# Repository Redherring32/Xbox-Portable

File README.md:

# Xbox-Portable
Fully portable original (2001) Xbox handheld using real hardware

## License:

Licensed under
the TAPR Open Hardware License (www.tapr.org/OHL)

©Redherring32 2023-2024

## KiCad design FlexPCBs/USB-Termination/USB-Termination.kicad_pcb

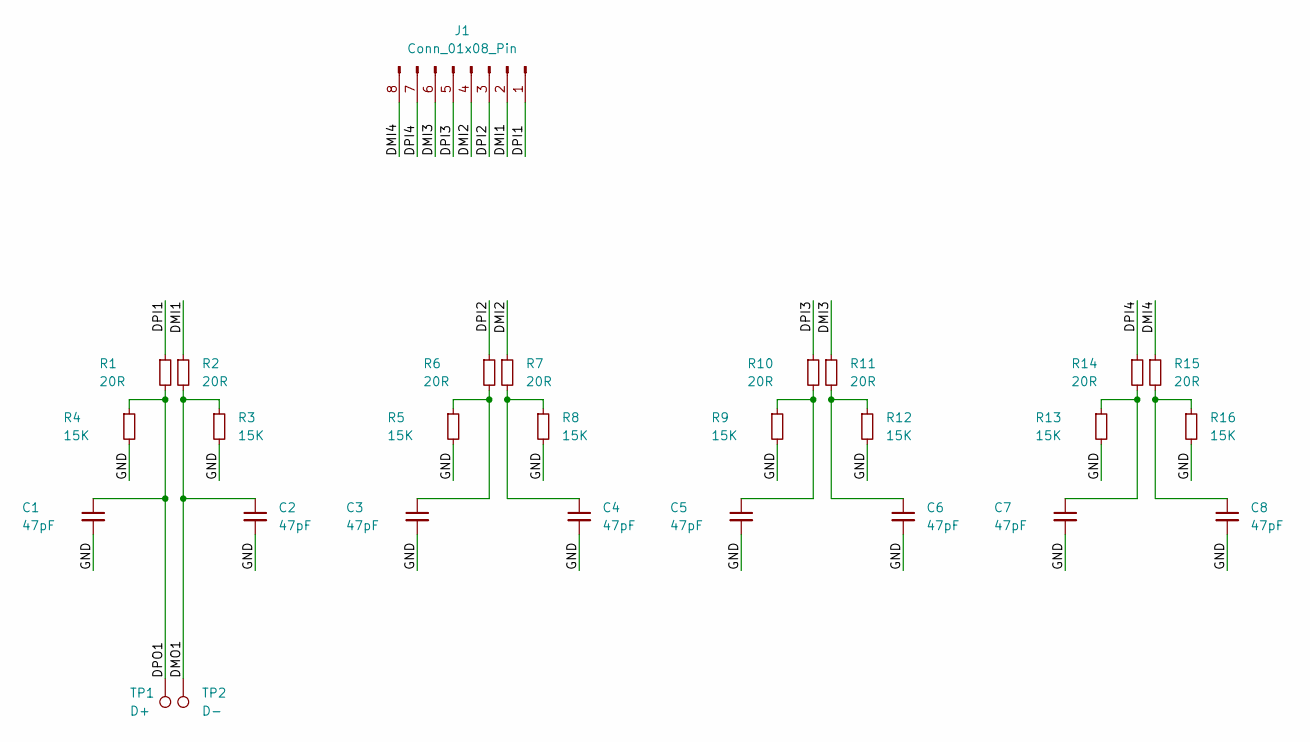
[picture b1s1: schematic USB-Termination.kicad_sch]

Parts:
C1, C2, C3, C4, C5, C6, C7, C8: 47pF; C_0201_0603Metric
J1: Conn_01x08_Pin; Vias
R1, R2, R6, R7, R10, R11, R14, R15: 20R; R_0201_0603Metric
R3, R4, R5, R8, R9, R12, R13, R16: 15K; R_0201_0603Metric
TP1: D+; TestPoint_Pad_D1.0mm
TP2: D-; TestPoint_Pad_D1.0mm

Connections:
/DMI1: J1.2, R2.1
/DMI2: J1.4, R7.1
/DMI3: J1.6, R11.1
/DMI4: J1.8, R15.1
/DMO1: C2.1, R2.2, R3.1, TP2.1
/DPI1: J1.1, R1.1
/DPI2: J1.3, R6.1
/DPI3: J1.5, R10.1
/DPI4: J1.7, R14.1
/DPO1: C1.1, R1.2, R4.1, TP1.1
/GND: C1.2, C2.2, C3.2, C4.2, C5.2, C6.2, C7.2, C8.2, R3.2, R4.2, R5.2, R8.2, R9.2, R12.2, R13.2, R16.2
unnamed: C3.1, R5.1, R6.2
unnamed: C4.1, R7.2, R8.1
unnamed: C5.1, R9.1, R10.2
unnamed: C6.1, R11.2, R12.1
unnamed: C7.1, R13.1, R14.2
unnamed: C8.1, R15.2, R16.1

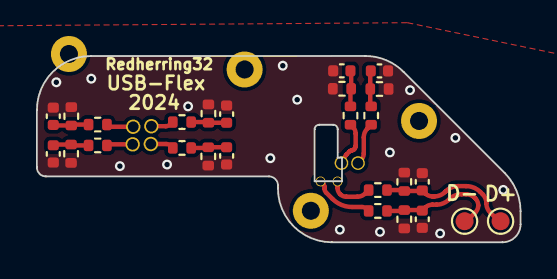
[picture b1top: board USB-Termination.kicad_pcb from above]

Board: 2 copper layers, 26.9 x 10.3 mm, 27 parts (1 on the bottom side), 17 nets.

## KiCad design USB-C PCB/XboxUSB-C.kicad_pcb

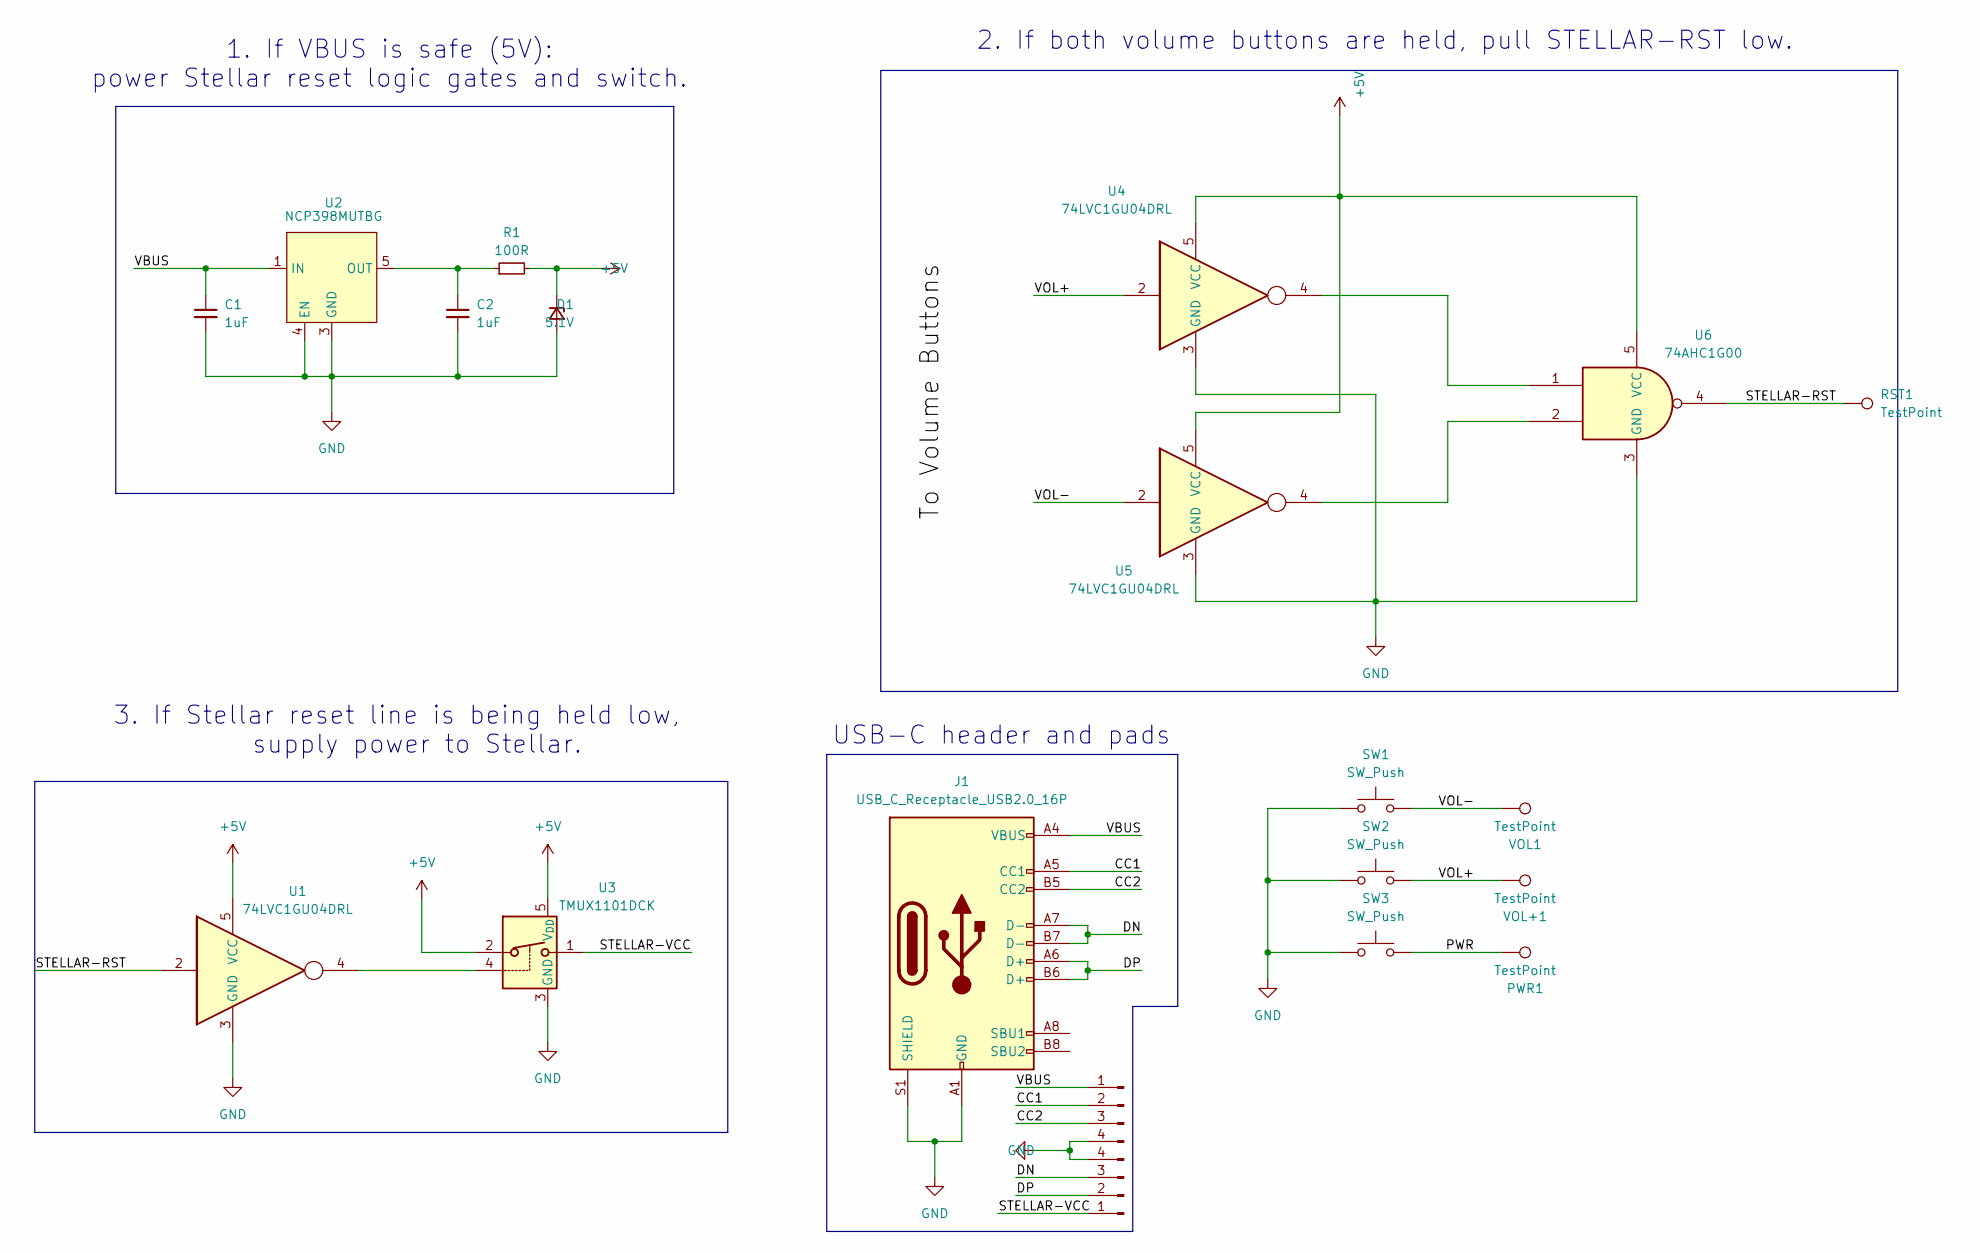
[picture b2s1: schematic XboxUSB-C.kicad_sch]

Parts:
C1, C2: 1uF; C_0805_2012Metric
D1: 5.1V; D_SOD-323_HandSoldering
J1: USB_C_Receptacle_USB2.0_16P; USB_C_Receptacle_GCT_USB4110
J2, J3: Conn_01x04_Pin; VBUS PADS
PWR1: TestPoint; TestPoint_Pad_D2.5mm
R1: 100R; R_0805_2012Metric
RST1: TestPoint; TestPoint_Pad_D2.5mm
SW1, SW2, SW3: SW_Push; SW_Tactile_SPST_Angled_PTS645Vx58-2LFS
U1, U4, U5: 74LVC1GU04DRL; SOT-553
U2: NCP398MUTBG; DFN-6-1EP_2x2mm_P0.65mm_EP1.01x1.7mm
U3: TMUX1101DCK; WSON-8-1EP_3x2.5mm_P0.5mm_EP1.2x1.5mm_PullBack
U6: 74AHC1G00; SOT-23-5
VOL1: TestPoint; TestPoint_Pad_D2.5mm
VOL+1: TestPoint; TestPoint_Pad_D2.5mm

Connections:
+5V: D1.1 (K), R1.2, U1.5 (VCC), U3.2, U3.5 (V_{DD}), U4.5 (VCC), U5.5 (VCC), U6.5 (VCC)
/CC1: J1.A5 (CC1), J3.2
/CC2: J1.B5 (CC2), J3.3
/DN: J1.A7 (D-), J1.B7 (D-), J2.3
/DP: J1.A6 (D+), J1.B6 (D+), J2.2
/PWR: PWR1.1, SW3.2
/STELLAR-RST: RST1.1, U1.2, U6.4
/STELLAR-VCC: J2.1, U3.1
/VOL+: SW2.2, U4.2, VOL+1.1
/VOL-: SW1.2, U5.2, VOL1.1; also elsewhere on the board
GND: C1.2, C2.2, D1.2 (A), J1.A1 (GND), J1.A12 (GND), J1.B1 (GND), J1.B12 (GND), J1.S1 (SHIELD), J2.4, J3.4, SW1.1, SW2.1, SW3.1, U1.3 (GND), U2.3 (GND), U2.4 (EN), U2.7 (PAD), U3.3 (GND), U3.9 (GND), U4.3 (GND), U5.3 (GND), U6.3 (GND)
IN: C1.1, J1.A4 (VBUS), J1.A9 (VBUS), J1.B4 (VBUS), J1.B9 (VBUS), J3.1, U2.1 (IN), U2.2 (IN)
unnamed: C2.1, R1.1, U2.5 (OUT), U2.6 (OUT)
unnamed: U1.4, U3.4
unnamed: U4.4, U6.1
unnamed: U5.4, U6.2

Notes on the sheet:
1. If VBUS is safe (5V): power Stellar reset logic gates and switch.
USB-C header and pads
2. If both volume buttons are held, pull STELLAR-RST low.
3. If Stellar reset line is being held low, supply power to Stellar.

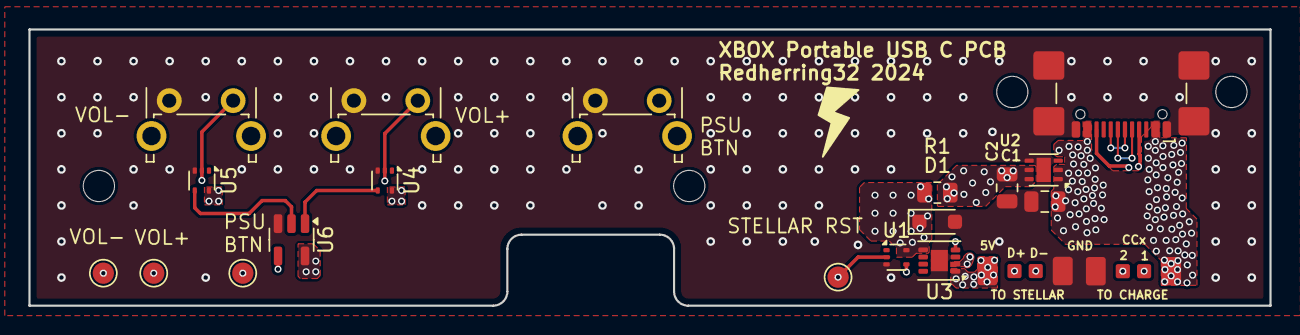
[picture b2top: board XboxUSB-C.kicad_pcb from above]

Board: 4 copper layers, 87.4 x 19.4 mm, 24 parts (0 on the bottom side), 16 nets.

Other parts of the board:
MH1, MH2, MH2#2, MH2#3: MountingHole_2.2mm_M2
VOL-1: TestPoint; TestPoint_Pad_D1.5mm

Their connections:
/VOL-: VOL-1.1; also elsewhere on the board

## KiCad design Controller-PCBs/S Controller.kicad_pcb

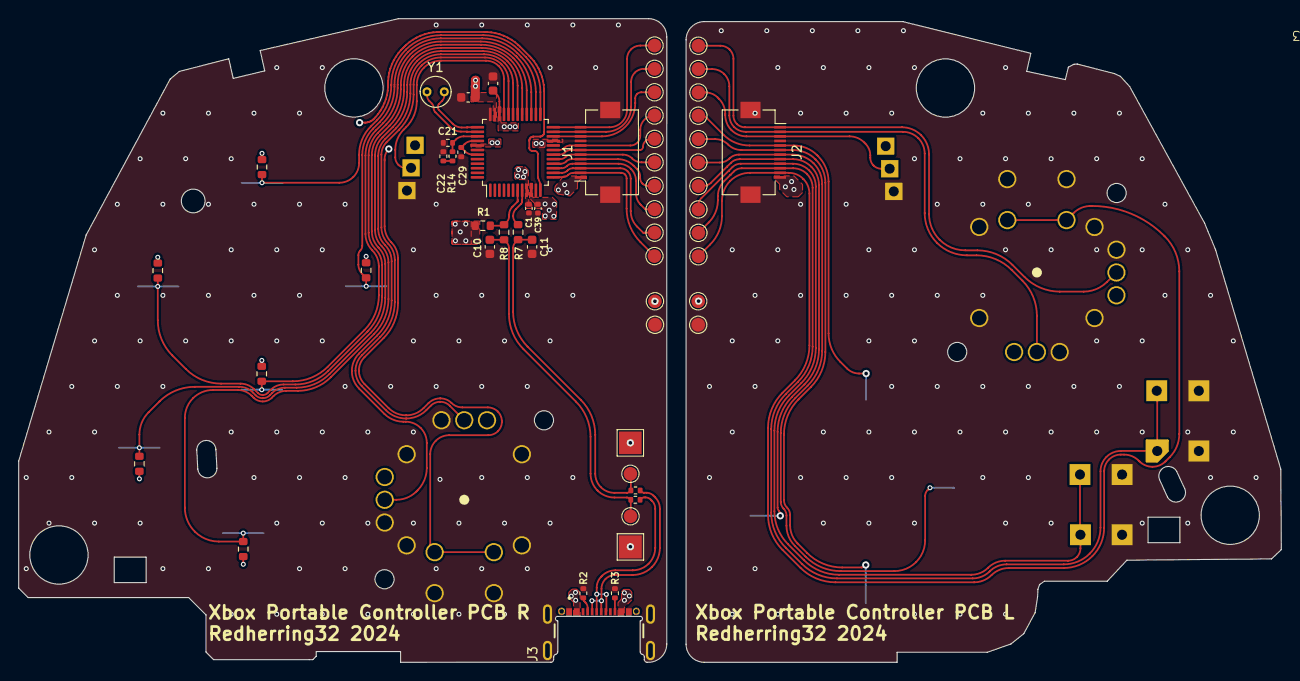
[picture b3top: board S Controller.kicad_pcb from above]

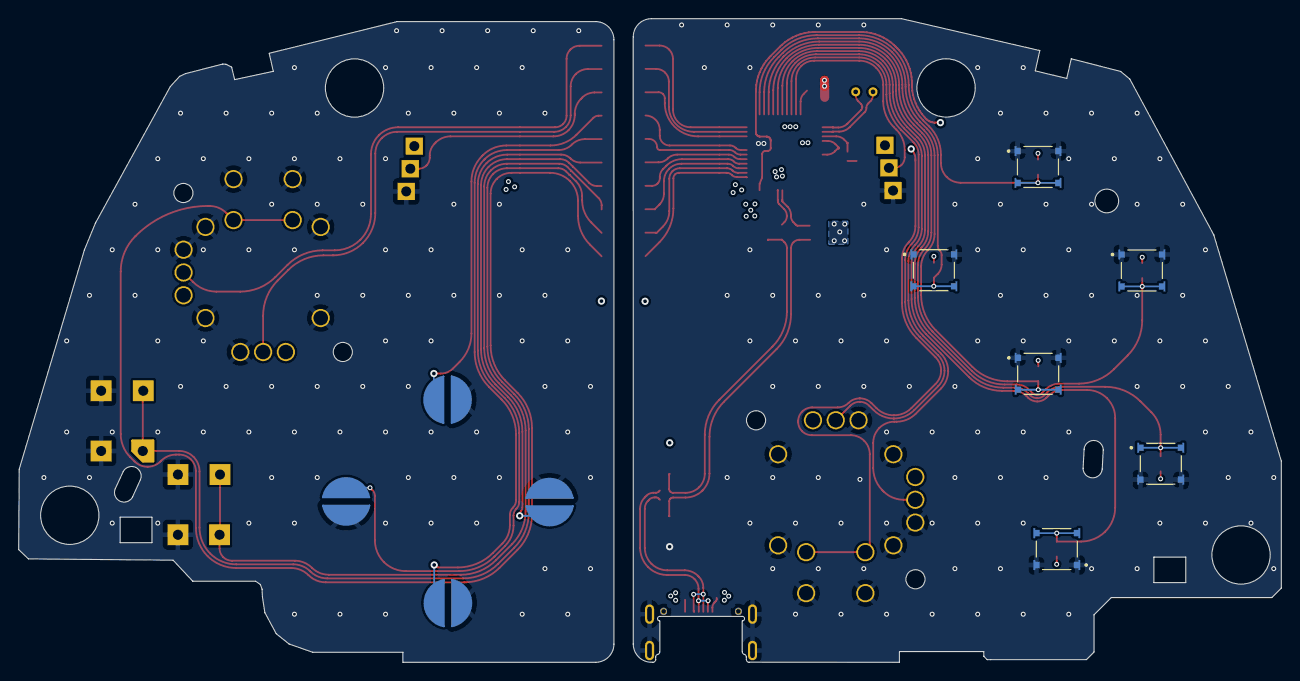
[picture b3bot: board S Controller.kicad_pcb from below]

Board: 4 copper layers, 138.6 x 70.7 mm, 70 parts (11 on the bottom side), 35 nets.

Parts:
C1: 2.2uF; C_0402_1005Metric
C10, C11: 50pF; C_0603_1608Metric
C21: 0.01uF; R_0402_1005Metric
C22: 0.1nF; R_0402_1005Metric
C29: 2.2uF; R_0402_1005Metric
C33: 0.1uF; C_0603_1608Metric
C36: 0.33uF; C_0603_1608Metric
C39: 0.01uF; C_0402_1005Metric
J1, J2: Conn_01x12_Pin; Hirose_FH12-12S-0.5SH_1x12-1MP_P0.50mm_Horizontal
J3: USB_C_Receptacle_USB2.0; GCT_USB4720-03-A_REVA
R1: 1.5K; R_0603_1608Metric
R2, R3: 5.1K; R_0402_1005Metric
R7, R8: 27R; R_0603_1608Metric
R14: 100R; R_0402_1005Metric
R17, R18, R24, R25, R31, R32: 4.7K; R_0603_1608Metric
RV1, RV2: R_Potentiometer_Small; TRIGGER-R
SW1, SW2, SW3, SW4, SW5, SW6: SW_Push; SW_TL3315NF100Q
SW7, SW8, SW9, SW10: SW_Push; DPADCONTACTS
SW11, SW12: SW_Push; StartBack
TP1, TP2, TP3, TP4, TP5, TP6, TP7, TP8, TP9, TP10, TP11, TP12, TP13, TP14, TP15, TP16, TP19, TP20, TP21, TP22, TP23, TP24, TP25, TP26, TP27, TP28: TestPoint; TestPoint_Pad_D1.5mm
TP17, TP18: TestPoint; TestPoint_Pad_2.5x2.5mm
U1: AT43USB353M-AC; LQFP-48_7x7mm_P0.5mm
U2, U3: RKJXV1224-Socket
Y1: 6MHz; Crystal_C38-LF_D3.0mm_L8.0mm_Vertical

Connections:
/Back: J1.3, J2.10, SW12.1, TP5.1, TP27.1, U1.14 (PA5)
/Black: R25.2, SW6.1, U1.29 (ADC4)
/ButtonA: R31.2, SW2.2, U1.27 (ADC6)
/ButtonB: R32.2, SW4.2, U1.28 (ADC5)
/ButtonX: R24.2, SW3.2, U1.26 (ADC7)
/ButtonY: R17.2, SW1.2, U1.25 (ADC8)
/CEXT1: C1.1, R1.2, U1.9 (CEXT1)
/CEXTA: C36.1, J1.1, J2.12, R17.1, R18.1, R24.1, R25.1, R31.1, R32.1, RV1.1, RV2.1, TP8.1, TP13.1, U1.35 (CEXTA), U2.5 (+), U2.8 (+), U3.5 (+), U3.8 (+)
/CPUSEL: C29.1, U1.40 (CEXT2), U1.43 (CPUSEL)
/D+: R1.1, R8.1, U1.7 (DP0)
/D-: R7.1, U1.8 (DM0)
/DpadD: J1.7, J2.6, SW8.1, TP4.1, TP23.1, U1.18 (PA1)
/DpadL: J1.6, J2.7, SW10.1, TP2.1, TP24.1, U1.17 (PA2)
/DpadR: J1.5, J2.8, SW9.1, TP3.1, TP25.1, U1.16 (PA3)
/DpadU: J1.8, J2.5, SW7.1, TP1.1, TP22.1, U1.19 (PA0)
/IN+: C10.1, J3.A6 (D+), J3.B6 (D+), R8.2, TP16.1
/IN-: C11.1, J3.A7 (D-), J3.B7 (D-), R7.2, TP15.1
/LFT: C21.1, R14.2, U1.39 (LFT)
/LStickX: J1.11, J2.2, TP9.1, TP20.1, U1.23 (ADC10), U3.7 (X)
/LStickY: J1.12, J2.1, TP10.1, TP19.1, U1.24 (ADC9), U3.4 (Y)
/RStickX: U1.32 (ADC1), U2.7 (X)
/RStickY: U1.31 (ADC2), U2.4 (Y)
/SClickL: J1.2, J2.11, TP11.1, TP28.1, U1.13 (PA6), U3.1
/SClickR: U1.12 (PA7), U2.1
/Start: J1.4, J2.9, SW11.1, TP6.1, TP26.1, U1.15 (PA4)
/TriggerL: J1.10, J2.3, RV2.2, TP12.1, TP21.1, U1.22 (ADC11)
/TriggerR: RV1.2, U1.33 (ADC0)
/VCC: C33.1, C39.1, J3.A4 (VBUS), J3.B4 (VBUS), TP17.1, U1.10 (VCC1), U1.34 (VCCA), U1.41 (VCC2)
/White: R18.2, SW5.2, U1.30 (ADC3)
/XTAL+: U1.37 (XTAL1), Y1.2
/XTAL-: U1.38 (XTAL2), Y1.1
GND: C1.2, C10.2, C11.2, C21.2, C22.1, C29.2, C33.2, C36.2, C39.2, J1.9, J1.MP, J2.4, J2.MP, J3.A12 (GND), J3.B12 (GND), J3.S1 (SHIELD), R2.2, R3.2, RV1.3, RV2.3, SW1.1, SW2.1, SW3.1, SW4.1, SW5.1, SW6.2, SW7.2, SW8.2, SW9.2, SW10.2, SW11.2, SW12.2, TP7.1, TP14.1, TP18.1, U1.11 (VSS1), U1.21 (TEST), U1.36 (VSSA), U1.42 (VSS2), U2.2, U2.3 (-), U2.6 (-), U3.2, U3.3 (-), U3.6 (-)
unnamed: C22.2, R14.1
unnamed: J3.A5 (CC1), R2.1
unnamed: J3.B5 (CC2), R3.1

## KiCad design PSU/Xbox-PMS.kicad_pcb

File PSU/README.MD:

This is a preliminary version of the Xbox Power Management System used in this portable Xbox design.
It does not yet have charging built in, but can be used in its current state as a compact power supply for revision 121 Xbox motherboards that have both the stock regulators removed, as well as standby disabled.

For info on identifying a 121 Xbox PCB you can read this guide here: https://www.herringhardware.com/XboxRevisions.html
For info on disabling standby and removing stock regulators on a 121 motherboard you can read this guide: https://bitbuilt.net/forums/index.php?threads/xbox-trimming-guide.6157/

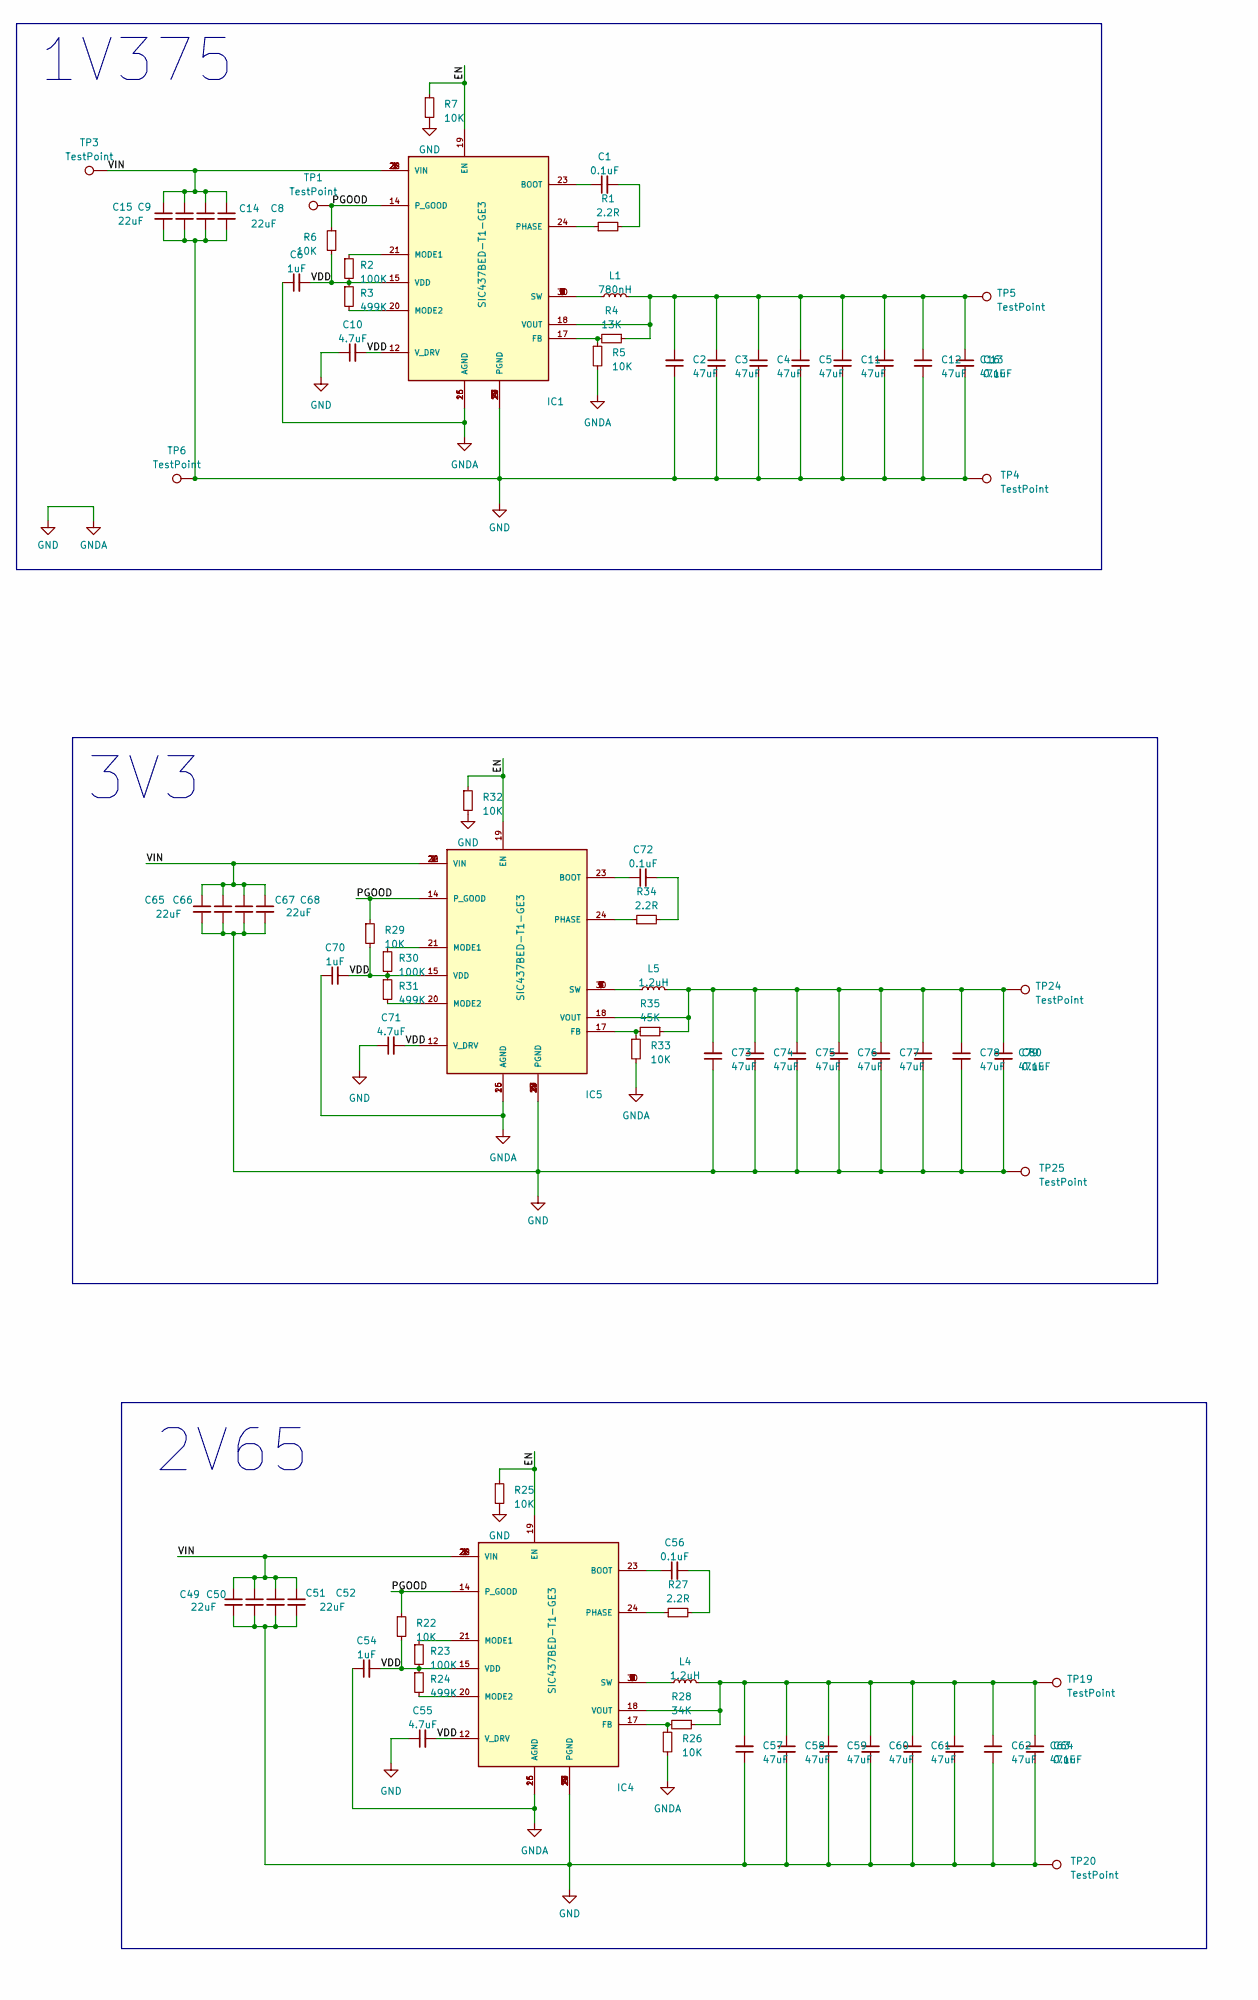
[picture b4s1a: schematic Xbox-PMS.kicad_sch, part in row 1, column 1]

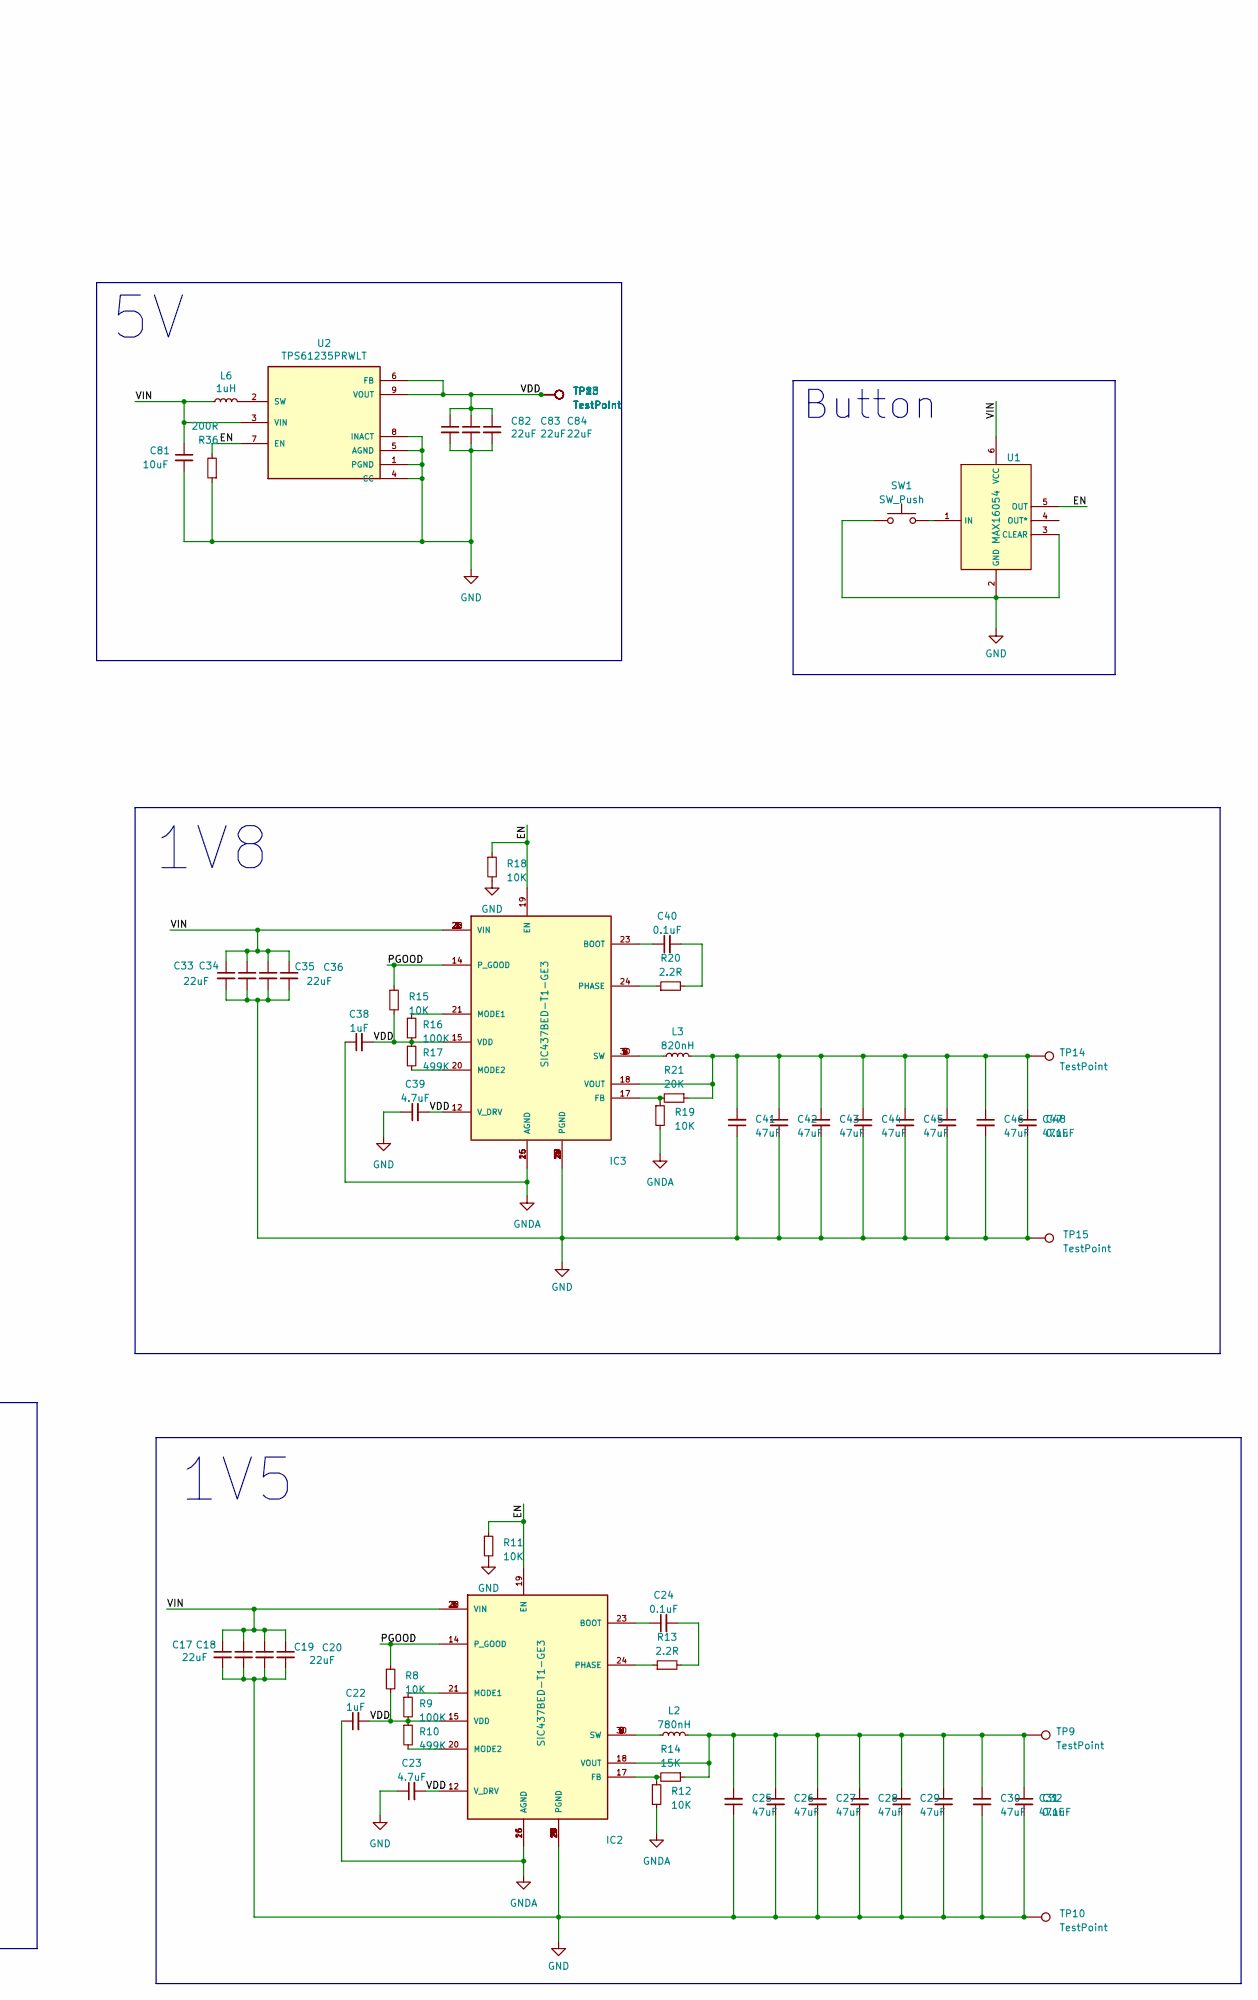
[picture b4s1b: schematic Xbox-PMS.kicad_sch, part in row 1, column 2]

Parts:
C1, C24, C40, C56, C72: 0.1uF; C_0402_1005Metric
C2, C3, C4, C25, C26, C27, C41, C42, C43, C57, C58, C59, C73, C74, C75: 47uF; C_1210_3225Metric
C5, C11, C12, C16, C28, C29, C30, C31, C44, C45, C46, C47, C60, C61, C62, C63, C76, C77, C78, C79: 47uF; C_0603_1608Metric
C6, C22, C38, C54, C70: 1uF; C_0402_1005Metric
C8, C20, C36, C52, C68, C82, C83, C84: 22uF; C_0603_1608Metric
C9, C14, C15, C17, C18, C19, C33, C34, C35, C49, C50, C51, C65, C66, C67: 22uF; C_1210_3225Metric
C10, C23, C39, C55, C71: 4.7uF; C_0603_1608Metric
C13, C32, C48, C64, C80: 0.1uF; C_0603_1608Metric
C81: 10uF; C_0603_1608Metric
IC1, IC2, IC3, IC4, IC5: SIC437BED-T1-GE3; SIC437BEDT1GE3
L1, L2: 780nH; L_7.3x7.3_H4.5
L3: 820nH; L_7.3x7.3_H4.5
L4, L5: 1.2uH; L_7.3x7.3_H4.5
L6: 1uH; L_7.3x7.3_H4.5
R1, R13, R20, R27, R34: 2.2R; R_0402_1005Metric
R2, R9, R16, R23, R30: 100K; R_0402_1005Metric
R3, R10, R17, R24, R31: 499K; R_0402_1005Metric
R4: 13K; R_0402_1005Metric
R5, R6, R7, R8, R11, R12, R15, R18, R19, R22, R25, R26, R29, R32, R33: 10K; R_0402_1005Metric
R14: 15K; R_0402_1005Metric
R21: 20K; R_0402_1005Metric
R28: 34K; R_0402_1005Metric
R35: 45K; R_0402_1005Metric
R36: 200R; R_0805_2012Metric
SW1: SW_Push; Button
TP1, TP8, TP13, TP18, TP23: TestPoint; TestPoint_Pad_3.0x3.0mm
TP3, TP4, TP5, TP6, TP9, TP10, TP14, TP15, TP19, TP20, TP24, TP25: TestPoint; pad
U1: MAX16054; SOT-23-6
U2: TPS61235PRWLT; CONV_TPS61235PRWLT

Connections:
/EN: IC1.19 (EN), IC2.19 (EN), IC3.19 (EN), IC4.19 (EN), IC5.19 (EN), R7.1, R11.1, R18.1, R25.1, R32.1, R36.2, U1.5 (OUT), U2.7 (EN)
/PGOOD: IC1.14 (P_GOOD), IC2.14 (P_GOOD), IC3.14 (P_GOOD), IC4.14 (P_GOOD), IC5.14 (P_GOOD), R6.1, R8.1, R15.1, R22.1, R29.1, TP1.1
unnamed: C1.2, R1.2
unnamed: C24.2, R13.2
unnamed: C40.2, R20.2
unnamed: C56.2, R27.2
unnamed: C72.2, R34.2
unnamed: C1.1, IC1.23 (BOOT)
unnamed: IC1.17 (FB), R4.2, R5.1
unnamed: IC1.21 (MODE1), R2.1
unnamed: IC1.20 (MODE2), R3.2
unnamed: IC1.24 (PHASE), R1.1
unnamed: IC1.5 (SW), IC1.6 (SW), IC1.7 (SW), IC1.8 (SW), IC1.9 (SW), IC1.30 (SW), L1.1
unnamed: C2.2, C3.1, C4.1, C5.1, C11.1, C12.1, C13.1, C16.1, IC1.18 (VOUT), L1.2, R4.1, TP5.1
unnamed: C24.1, IC2.23 (BOOT)
unnamed: IC2.17 (FB), R12.1, R14.2
unnamed: IC2.21 (MODE1), R9.1
unnamed: IC2.20 (MODE2), R10.2
unnamed: IC2.24 (PHASE), R13.1
unnamed: IC2.5 (SW), IC2.6 (SW), IC2.7 (SW), IC2.8 (SW), IC2.9 (SW), IC2.30 (SW), L2.1
unnamed: C25.2, C26.1, C27.1, C28.1, C29.1, C30.1, C31.1, C32.1, IC2.18 (VOUT), L2.2, R14.1, TP9.1
unnamed: C40.1, IC3.23 (BOOT)
unnamed: IC3.17 (FB), R19.1, R21.2
unnamed: IC3.21 (MODE1), R16.1
unnamed: IC3.20 (MODE2), R17.2
unnamed: IC3.24 (PHASE), R20.1
unnamed: IC3.5 (SW), IC3.6 (SW), IC3.7 (SW), IC3.8 (SW), IC3.9 (SW), IC3.30 (SW), L3.1
unnamed: C41.2, C42.1, C43.1, C44.1, C45.1, C46.1, C47.1, C48.1, IC3.18 (VOUT), L3.2, R21.1, TP14.1
unnamed: C56.1, IC4.23 (BOOT)
unnamed: IC4.17 (FB), R26.1, R28.2
unnamed: IC4.21 (MODE1), R23.1
unnamed: IC4.20 (MODE2), R24.2
unnamed: IC4.24 (PHASE), R27.1
unnamed: IC4.5 (SW), IC4.6 (SW), IC4.7 (SW), IC4.8 (SW), IC4.9 (SW), IC4.30 (SW), L4.1
unnamed: C57.2, C58.1, C59.1, C60.1, C61.1, C62.1, C63.1, C64.1, IC4.18 (VOUT), L4.2, R28.1, TP19.1
unnamed: C72.1, IC5.23 (BOOT)
unnamed: IC5.17 (FB), R33.1, R35.2
unnamed: IC5.21 (MODE1), R30.1
unnamed: IC5.20 (MODE2), R31.2
unnamed: IC5.24 (PHASE), R34.1
unnamed: IC5.5 (SW), IC5.6 (SW), IC5.7 (SW), IC5.8 (SW), IC5.9 (SW), IC5.30 (SW), L5.1
unnamed: C73.2, C74.1, C75.1, C76.1, C77.1, C78.1, C79.1, C80.1, IC5.18 (VOUT), L5.2, R35.1, TP24.1
unnamed: SW1.2, U1.1 (IN)
unnamed: L6.2, U2.2 (SW)

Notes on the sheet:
1V5
1V375
Button
1V8
2V65
3V3

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
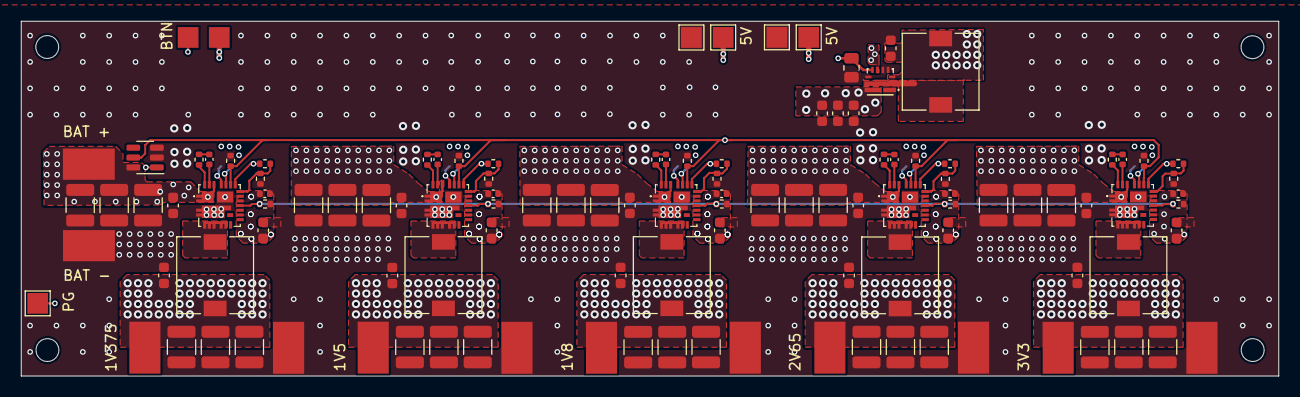
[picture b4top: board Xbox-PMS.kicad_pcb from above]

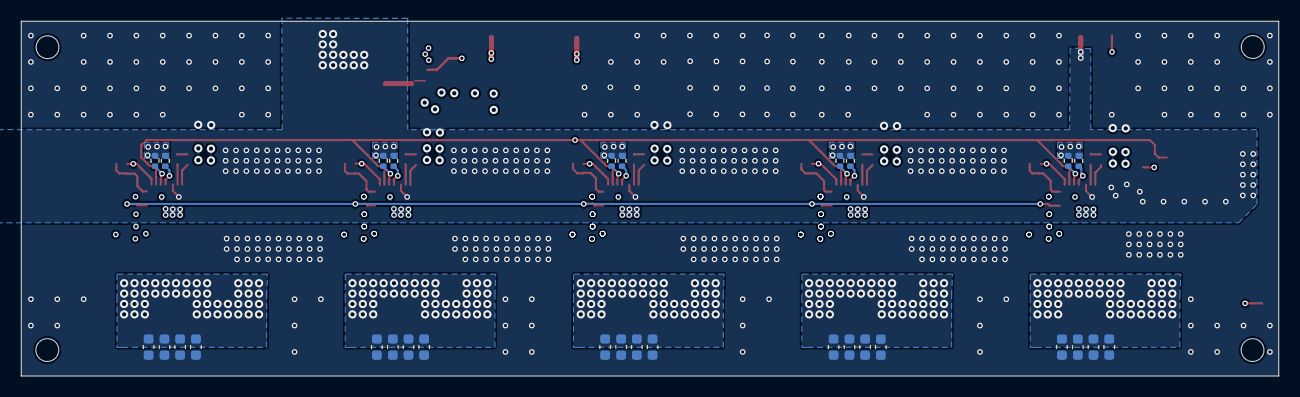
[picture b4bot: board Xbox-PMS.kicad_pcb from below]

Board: 13 copper layers, 121.2 x 34.2 mm, 150 parts (30 on the bottom side), 47 nets.

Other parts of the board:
 : MountingHole_2.2mm_M2
 #2,  #3,  #4: MountingHole_2.2mm_M2
TP18#2, TP18#3: TestPoint; TestPoint_Pad_2.0x2.0mm

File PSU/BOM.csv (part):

Query,Qty,Manufacturer,MPN,Octopart URL,Part Description,Description,Schematic Reference,Internal Part Number,Lifecycle,Lead Time,RoHS,Total Qty (@ Batch Size: 1),SKU,SKU,SKU,SKU,SKU,Packaging,Packaging,Packaging,Packaging,Packaging,Unit Price (@ Batch Size: 1),Unit Price (@ Batch Size: 1),Unit Price (@ Batch Size: 1),Unit Price (@ Batch Size: 1),Unit Price (@ Batch Size: 1),In Stock,In Stock,In Stock,In Stock,In Stock,MOQ,MOQ,MOQ,MOQ,MOQ,URL,URL,URL,URL,URL,Distributor [Lowest Price (Selected)],SKU [Lowest Price (Selected)],Packaging [Lowest Price (Selected)],Unit Price (@ Batch Size: 1) [Lowest Price (Selected)],Line Total [Lowest Price (Selected)],Batch Total [Lowest Price (Selected)],In Stock [Lowest Price (Selected)],MOQ [Lowest Price (Selected)],URL [Lowest Price (Selected)],Notes
,,,,,,,,,,,,,Digi-Key,Mouser,Newark,Onlinecomponents.com,RS Components,Digi-Key,Mouser,Newark,Onlinecomponents.com,RS Components,Digi-Key,Mouser,Newark,Onlinecomponents.com,RS Components,Digi-Key,Mouser,Newark,Onlinecomponents.com,RS Components,Digi-Key,Mouser,Newark,Onlinecomponents.com,RS Components,Digi-Key,Mouser,Newark,Onlinecomponents.com,RS Components,,,,,,,,,,
KGM05AR71C104JN,5,KYOCERA AVX,KGM05AR71C104JN,https://octopart.com/kgm05ar71c104jn-kyocera+avx-137404918,Cap Cer 0.1UF 16V X7R 0402,0.1uF,"C1, C24, C40, C56, C72",,,,,5,,,,,,,,,,,,,,,,,,,,,,,,,,,,,,,,,,,,,,,,
GRM32EC81A476KE19L,15,Murata,GRM32EC81A476KE19L,https://octopart.com/grm32ec81a476ke19l-murata-18041261,"Multilayer Ceramic Capacitor, 47 uF, 10 V, ± 10%, X6S, 1210 [3225 Metric]",47uF,"C2, C3, C4, C25, C26, C27, C41, C42, C43, C57, C58, C59, C73, C74, C75",,Production (Last Updated: 1 month ago),19w,Compliant,15,490-8354-1-ND,81-GRM32EC81A476KE9L,43T5299,,,Cut Tape,Tape & Reel,Cut Tape,,,0.289,0.463,0.482,,,43324,3526,709,,,1,1,1,,,https://octopart.com/opatz8j6/a1?t=kr73VKsF0eFVmfKHZ4VS-RGAo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,https://octopart.com/opatz8j6/a1?t=Xfg0vpCUlGH4kogXOWX5BVDIZ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,https://octopart.com/opatz8j6/a1?t=0aqwJpospI2puJjWHy9080wfP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,,,DigiKey,490-8354-1-ND,Cut Tape,0.289,4.335,4.335,43324,1,https://octopart.com/opatz8j6/a1?t=kr73VKsF0eFVmfKHZ4VS-RGAo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,
CL10A226MO7JZNC,28,Samsung,CL10A226MO7JZNC,https://octopart.com/cl10a226mo7jznc-samsung-82337114,"Multilayer Ceramic Capacitor, 22 uF, 16 V, ± 20%, X5R, 0603 [1608 Metric]",47uF,"C5, C11, C12, C16, C28, C29, C30, C31, C44, C45, C46, C47, C60, C61, C62, C63, C76, C77, C78, C79, C8, C20, C36, C52, C68, C82, C83, C84",,Production (Last Updated: 4 years ago),22w,Non-Compliant,28,1276-7076-1-ND,187-CL10A226MO7JZNC,,,,Cut Tape,Tape & Reel,,,,0.398,0.317,,,,1140870,334159,,,,1,1,,,,https://octopart.com/opatz8j6/a1?t=NNKHSNYTU6FRQN6Q77xOKoeol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,https://octopart.com/opatz8j6/a1?t=OtB6GASyGQNjwRlIAXYpGx-gR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,,,,Mouser,187-CL10A226MO7JZNC,Tape & Reel,0.317,8.876,8.876,334159,1,https://octopart.com/opatz8j6/a1?t=OtB6GASyGQNjwRlIAXYpGx-gR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,
CL05A105KO5NNNC,5,Samsung,CL05A105KO5NNNC,https://octopart.com/cl05a105ko5nnnc-samsung-9301309,"Multilayer Ceramic Capacitor, 1 uF, 16 V, ± 10%, X5R, 0402 [1005 Metric]",1uF,"C6, C22, C38, C54, C70",,Production (Last Updated: 4 years ago),22w,Compliant,5,1276-1067-1-ND,187-CL05A105KO5NNNC,82AC9181,,,Cut Tape,Tape & Reel,Cut Tape,,,0.1,0.1,0.104,,,3677274,281660,14503,,,1,1,1,,,https://octopart.com/opatz8j6/a1?t=t7jA65Wx3WgrkPciuh8zIeNSO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,https://octopart.com/opatz8j6/a1?t=HAbsTUtoBJXEJFnocSt8Xej4f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,https://octopart.com/opatz8j6/a1?t=RnOw0BFNY1IdVP-bmTv_uDRS7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,,,DigiKey,1276-1067-1-ND,Cut Tape,0.1,0.5,0.5,3677274,1,https://octopart.com/opatz8j6/a1?t=t7jA65Wx3WgrkPciuh8zIeNSO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,
CL32A226KPJNNNE,15,Samsung,CL32A226KPJNNNE,https://octopart.com/cl32a226kpjnnne-samsung-20879308,Cap Ceramic 22uF 10V X5R 10% SMD 1210 85°C Embossed T/R,22uF,"C9, C14, C15, C17, C18, C19, C33, C34, C35, C49, C50, C51, C65, C66, C67",,Production (Last Updated: 4 years ago),22w,Compliant,15,1276-3372-1-ND,187-CL32A226KPJNNNE,,,,Cut Tape,Tape & Reel,,,,0.198,0.147,,,,324463,119352,,,,1,1,,,,https://octopart.com/opatz8j6/a1?t=iYnO-ouTQgSGvnVwFVjz6IN64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,https://octopart.com/opatz8j6/a1?t=TqLScD3EyJjmvplfObqCIPgVg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,,,,Mouser,187-CL32A226KPJNNNE,Tape & Reel,0.147,2.205,2.205,119352,1,https://octopart.com/opatz8j6/a1?t=TqLScD3EyJjmvplfObqCIPgVg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,
CL10A475KP8NNNC,6,Samsung,CL10A475KP8NNNC,https://octopart.com/cl10a475kp8nnnc-samsung-9301844,"Multilayer Ceramic Capacitor, 4.7 uF, 10 V, ± 10%, X5R, 0603 [1608 Metric]",4.7uF,"C10, C23, C39, C55, C71, C88",,Production (Last Updated: 4 years ago),22w,Compliant,6,1276-1044-1-ND,187-CL10A475KP8NNNC,82AC9299,,,Cut Tape,Tape & Reel,Cut Tape,,,0.1,0.1,0.104,,,7501831,1131283,5722,,,1,1,1,,,https://octopart.com/opatz8j6/a1?t=b9Ojf8q3AmL6s9ELcLqxl1sd3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,https://octopart.com/opatz8j6/a1?t=ZkgkVfC8TC-yEh6yz4vCqBrme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,https://octopart.com/opatz8j6/a1?t=27xyBY1rnb2PT_t2eQp_xuJ9p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,,,DigiKey,1276-1044-1-ND,Cut Tape,0.1,0.6000000000000001,0.6000000000000001,7501831,1,https://octopart.com/opatz8j6/a1?t=b9Ojf8q3AmL6s9ELcLqxl1sd3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,
CL10B104KB8NNNL,5,Samsung,CL10B104KB8NNNL,https://octopart.com/cl10b104kb8nnnl-samsung-21395620,"Multilayer Ceramic Capacitor, 0.1 uF, 50 V, ± 10%, X7R, 0603 [1608 Metric]",0.1uF,"C13, C32, C48, C64, C80",,Production (Last Updated: 4 years ago),22w,Compliant,5,1276-CL10B104KB8NNNLCT-ND,187-CL10B104KB8NNNL,,,,Cut Tape,Tape & Reel,,,,0.1,0.1,,,,2569681,390005,,,,1,1,,,,https://octopart.com/opatz8j6/a1?t=K5i2kyA5ZhEslmDmTZS0SuB6S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,https://octopart.com/opatz8j6/a1?t=qlFvxJL_CWLDRxEGZJ8TKQOOw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,,,,DigiKey,1276-CL10B104KB8NNNLCT-ND,Cut Tape,0.1,0.5,0.5,2569681,1,https://octopart.com/opatz8j6/a1?t=K5i2kyA5ZhEslmDmTZS0SuB6S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,
GRM188R61E106MA73J,4,Murata,GRM188R61E106MA73J,https://octopart.com/grm188r61e106ma73j-murata-46693355,"Multilayer Ceramic Capacitor, 10 uF, 25 V, ± 20%, X5R, 0603 [1608 Metric]",10uF,"C81, C86, C89, C90",,Production (Last Updated: 1 month ago),19w,Compliant,4,490-12737-1-ND,81-GRM188R61E106MA3J,,,,Cut Tape,Tape & Reel,,,,0.29,0.28,,,,93315,61644,,,,1,1,,,,https://octopart.com/opatz8j6/a1?t=RROgy0eAXEhduCVEiXdSOAVCe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,https://octopart.com/opatz8j6/a1?t=3TrmHphHf-woRKr5JSQ4Qb5IG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,,,,Mouser,81-GRM188R61E106MA3J,Tape & Reel,0.28,1.12,1.12,61644,1,https://octopart.com/opatz8j6/a1?t=3TrmHphHf-woRKr5JSQ4Qb5IG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,
C1608X7R1E105K080AB,1,TDK,C1608X7R1E105K080AB,https://octopart.com/c1608x7r1e105k080ab-tdk-25947659,"Multilayer Ceramic Capacitor, 1 uF, 25 V, ± 10%, X7R, 0603 [1608 Metric]",1uF,C85,,Production (Last Updated: 1 year ago),24w,Compliant,1,445-5956-1-ND,810-C1608X7R1E105K,04X3256,,,Cut Tape,Tape & Reel,,,,0.19,0.19,0.223,,,212176,5918,2,,,1,1,1,,,https://octopart.com/opatz8j6/a1?t=Yf-LCX8KgokM70A7PHDwY7fsX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,https://octopart.com/opatz8j6/a1?t=-j60n8ISBY-5fPuTsdhNh1D9C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,https://octopart.com/opatz8j6/a1?t=EadEUfuUVEgP9-Z2mveV8-BN8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,,,DigiKey,445-5956-1-ND,Cut Tape,0.19,0.19,0.19,212176,1,https://octopart.com/opatz8j6/a1?t=Yf-LCX8KgokM70A7PHDwY7fsX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,
CL10B473KO8NNNC,1,Samsung,CL10B473KO8NNNC,https://octopart.com/cl10b473ko8nnnc-samsung-9291615,Cap Ceramic 0.047uF 16V X7R 10% SMD 0603 125°C Paper T/R,47nF,C87,,Production (Last Updated: 4 years ago),22w,Compliant,1,1276-2079-1-ND,187-CL10B473KO8NNNC,,,,Cut Tape,Tape & Reel,,,,0.1,0.1,,,,1168873,7121,,,,1,1,,,,https://octopart.com/opatz8j6/a1?t=OW-wqXUu5SsHz-cyhtKDoPL9l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,https://octopart.com/opatz8j6/a1?t=VPupn-6obvmnZa6JE4lWEK3cg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,,,,DigiKey,1276-2079-1-ND,Cut Tape,0.1,0.1,0.1,1168873,1,https://octopart.com/opatz8j6/a1?t=OW-wqXUu5SsHz-cyhtKDoPL9l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,
SIC437DED-T1-GE3,5,Vishay,SIC437DED-T1-GE3,https://octopart.com/sic437ded-t1-ge3-vishay-91387604,"3-28V input, 12A microBUCK with Internal compensation, External Bias, 50 µA quie",SIC437BED-T1-GE3,"IC1, IC2, IC3, IC4, IC5",,,14w,Compliant,5,SIC437DED-T1-GE3CT-ND,78-SIC437DED-T1-GE3,,,,Cut Tape,Tape & Reel,,,,1.93,1.93,,,,7480,1737,,,,1,1,,,,https://octopart.com/opatz8j6/a1?t=wgtUacwaBIqQcXbzDazfwFcF0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,https://octopart.com/opatz8j6/a1?t=RGlL9l_1hQGwGu8EytsglCqZa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,,,,Mouser,78-SIC437DED-T1-GE3,Tape & Reel,1.93,9.65,9.65,1737,1,https://octopart.com/opatz8j6/a1?t=RGlL9l_1hQGwGu8EytsglCqZa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,
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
